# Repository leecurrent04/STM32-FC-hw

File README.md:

# NARAEON (나래온)

**NARAEON**은 인하대학교 모형항공기 동아리 '나래'(NARAE)에서 개발 중인 오픈소스 비행제어컴퓨터(FC) 프로젝트입니다. 이 프로젝트는 학술적 연구, 개발 그리고 취미 활동을 목적으로 하는 모든 분들을 위해 하드웨어, 펌웨어를 포함하고 있습니다.

## 🌟 프로젝트 소개
NARAEON은 무인항공기(UAV)의 핵심인 **비행제어컴퓨터**와 주요 센서들을 아우르는 통합 플랫폼입니다. 
저희는 항공전자 분야를 처음 배우는 학생들이 쉽게 학습하고 새로운 기능을 구현 및 창조할 수 있는 플랫폼을 제공하고자 이 프로젝트를 시작하게 되었습니다.

## ✨ 주요 특징
- 오픈소스: 하드웨어 회로도부터 펌웨어 소스 코드까지 모든 것이 공개되어 있어 누구나 자유롭게 사용하고, 수정하며, 기여할 수 있습니다.
- 통합 플랫폼: 비행 제어에 필요한 컴퓨터와 핵심 센서를 포함하여 안정적인 비행 제어 솔루션을 제공합니다.
- 확장성: 다양한 종류의 무인항공기에 적용할 수 있도록 설계되었으며, 사용자의 필요에 따라 기능을 쉽게 확장할 수 있습니다.
- 교육 및 연구: 학생, 연구자, 개발자들이 비행 제어 시스템의 원리를 깊이 있게 학습하고, 새로운 기술을 실험할 수 있는 훌륭한 교육 및 연구 도구입니다.

## 🚀 시작하기
프로젝트를 시작하는 데 필요한 정보는 각 저장소의 Wiki 페이지나 문서를 참고해 주세요. (링크 추가 예정)

하드웨어: [하드웨어 관련 저장소 링크]

- [STM32-FC](https://github.com/NARAE-INHA-UNIV/STM32-FC) : Firmware & Source code
- [NALDA](https://github.com/NARAE-INHA-UNIV/NALDA) : GCS

## 🔍 HW Spec.

> PCB 보드에 릴리즈 날짜와 버전이 기록되어 있지 않으면 v1.0.0 버전 입니다.
현재 최신 버전은 v1.1.0 입니다.

- ICM-45686 & ICM-42688-P dual IMU
- LIS2MDL eCompass
- ICP-20100 pressure sensor
- 내장 Flash memory & Micro SD card
- IBUS, SBUS, SRXL2, ELRS, PPM RC 프로토콜 지원

## 🤝 기여하기

NARAEON 프로젝트는 여러분의 참여를 언제나 환영합니다! 버그 리포트, 기능 제안, 코드 기여 등 어떤 형태의 기여도 프로젝트 발전에 큰 힘이 됩니다. 기여하고 싶으시다면 다음을 참고해 주세요.

1. 이 저장소를 Fork 하세요.
2. 새로운 기능이나 수정을 위한 Branch를 생성하세요 (git checkout -b feature/AmazingFeature).
3. 코드를 수정하고 Commit 하세요 (git commit -m 'Add some AmazingFeature').
4. Branch에 Push 하세요 (git push origin feature/AmazingFeature).
5. Pull Request를 열어주세요.

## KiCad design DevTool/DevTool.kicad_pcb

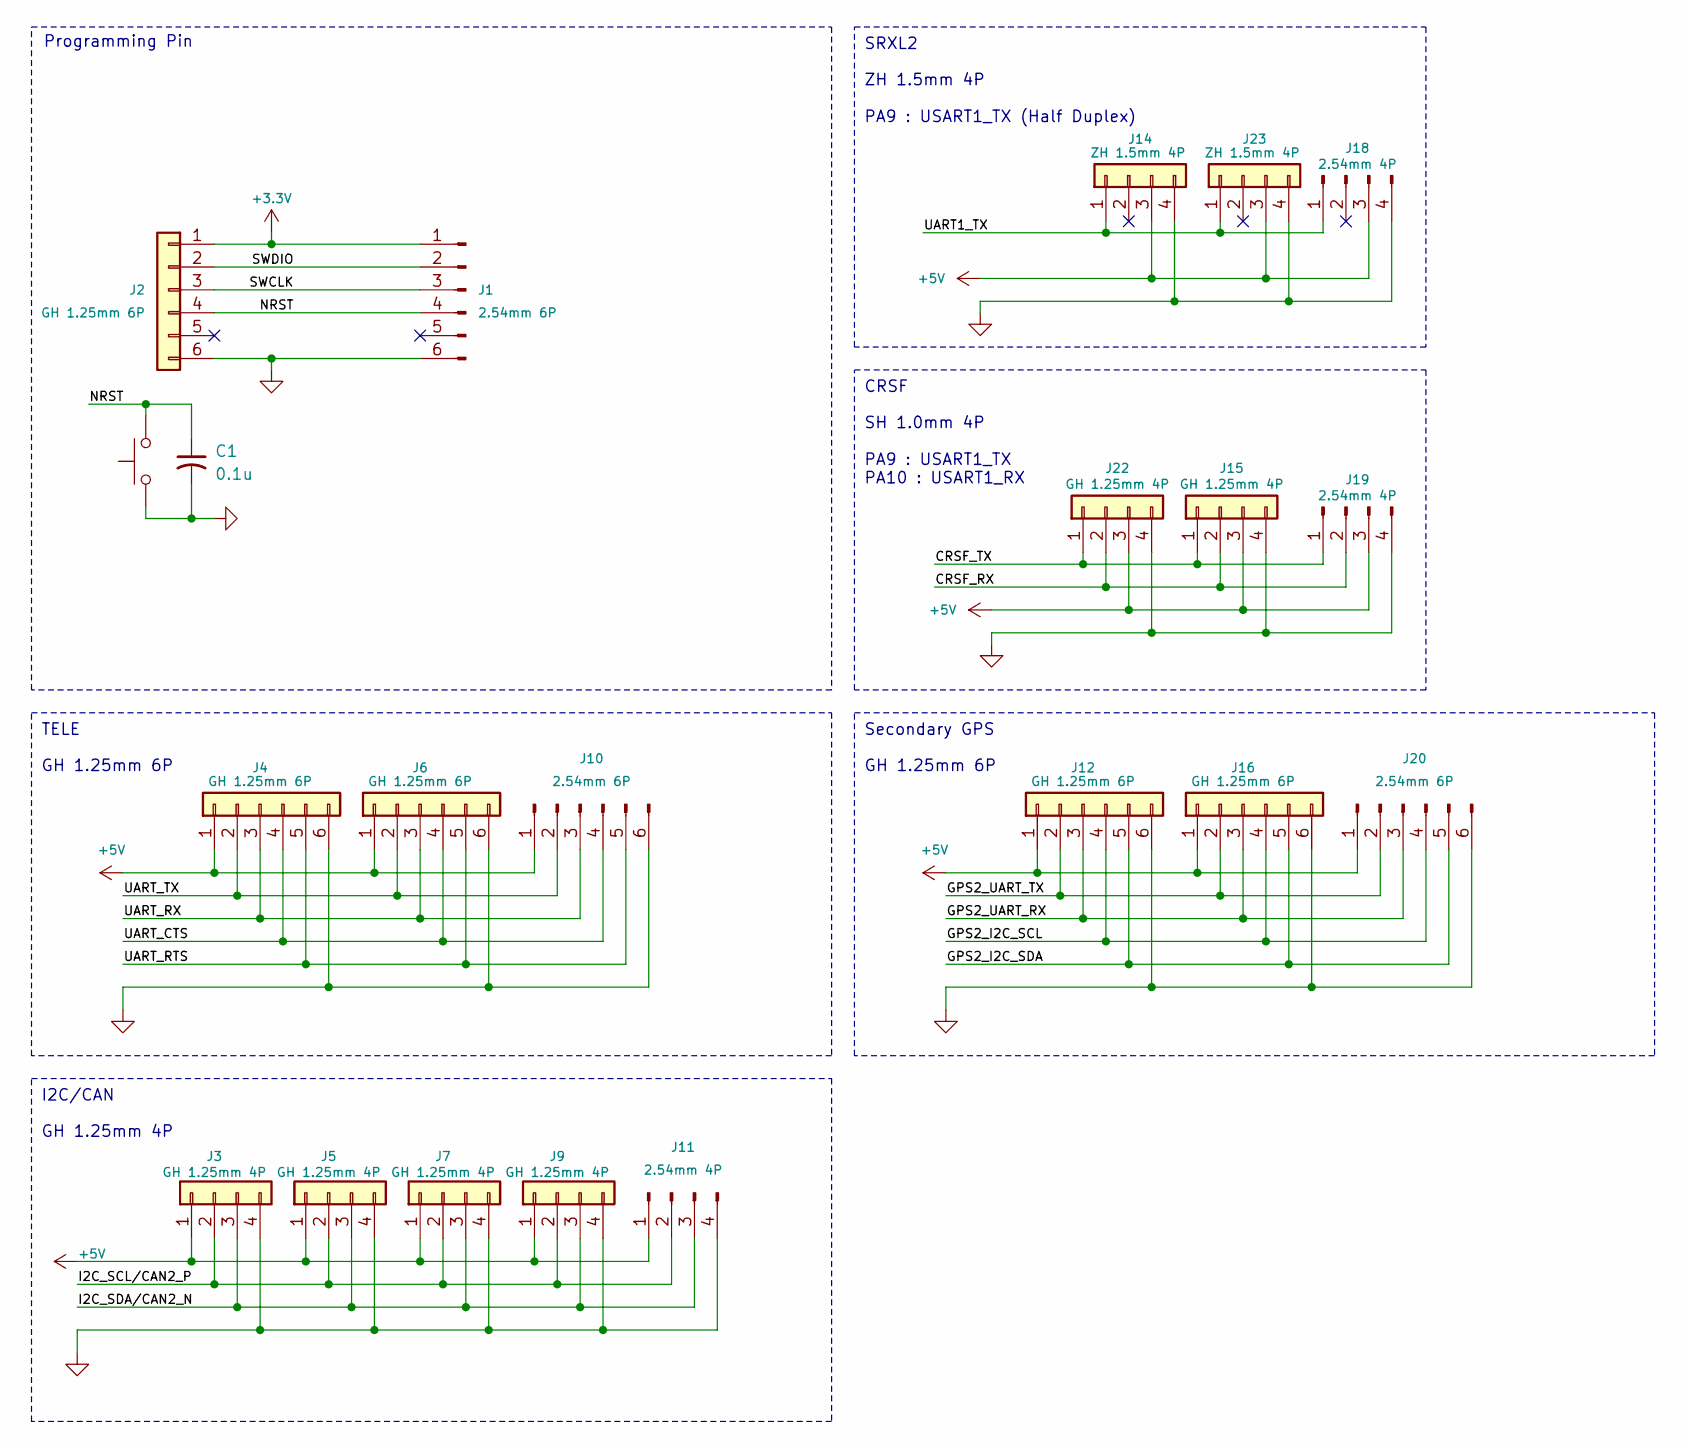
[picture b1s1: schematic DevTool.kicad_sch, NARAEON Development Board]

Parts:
C1: 0.1u; C_0603_1608Metric
J1, J10, J20: 2.54mm 6P; PinHeader_1x06_P2.54mm_Vertical
J2, J4, J6, J12, J16: GH 1.25mm 6P; JST_GH_BM06B-GHS-TBT_06; LCSC C133065
J3, J5, J7, J9, J15, J22: GH 1.25mm 4P; JST_GH_BM04B-GHS-TBT_04; LCSC C189895
J11, J18, J19: 2.54mm 4P; PinHeader_1x04_P2.54mm_Vertical
J14, J23: ZH 1.5mm 4P; JST_ZH_S4B-ZR-SM4A-TF_1x04-1MP_P1.50mm_Horizontal; LCSC C485354
SW1: SW_Push; SW_SPST_PTS645

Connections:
+3.3V: J1.1, J2.1
+5V: J3.1, J4.1, J5.1, J6.1, J7.1, J9.1, J10.1, J11.1, J12.1, J14.3, J15.3, J16.1, J18.3, J19.3, J20.1, J22.3, J23.3
/CRSF_RX: J15.2, J19.2, J22.2
/CRSF_TX: J15.1, J19.1, J22.1
/GPS2_I2C_SCL: J12.4, J16.4, J20.4
/GPS2_I2C_SDA: J12.5, J16.5, J20.5
/GPS2_UART_RX: J12.3, J16.3, J20.3
/GPS2_UART_TX: J12.2, J16.2, J20.2
/I2C_SCL/CAN2_P: J3.2, J5.2, J7.2, J9.2, J11.2
/I2C_SDA/CAN2_N: J3.3, J5.3, J7.3, J9.3, J11.3
/NRST: C1.1, J1.4, J2.4, SW1.2
/SWCLK: J1.3, J2.3
/SWDIO: J1.2, J2.2
/UART1_TX: J14.1, J18.1, J23.1
/UART_CTS: J4.4, J6.4, J10.4
/UART_RTS: J4.5, J6.5, J10.5
/UART_RX: J4.3, J6.3, J10.3
/UART_TX: J4.2, J6.2, J10.2
GND: C1.2, J1.6, J2.6, J3.4, J4.6, J5.4, J6.6, J7.4, J9.4, J10.6, J11.4, J12.6, J14.4, J15.4, J16.6, J18.4, J19.4, J20.6, J22.4, J23.4, SW1.1

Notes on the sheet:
SRXL2
CRSF
SH 1.0mm 4P PA9 : USART1_TX PA10 : USART1_RX
GH 1.25mm 6P
Programming Pin
TELE
GH 1.25mm 4P
I2C/CAN
Secondary GPS
ZH 1.5mm 4P PA9 : USART1_TX (Half Duplex)

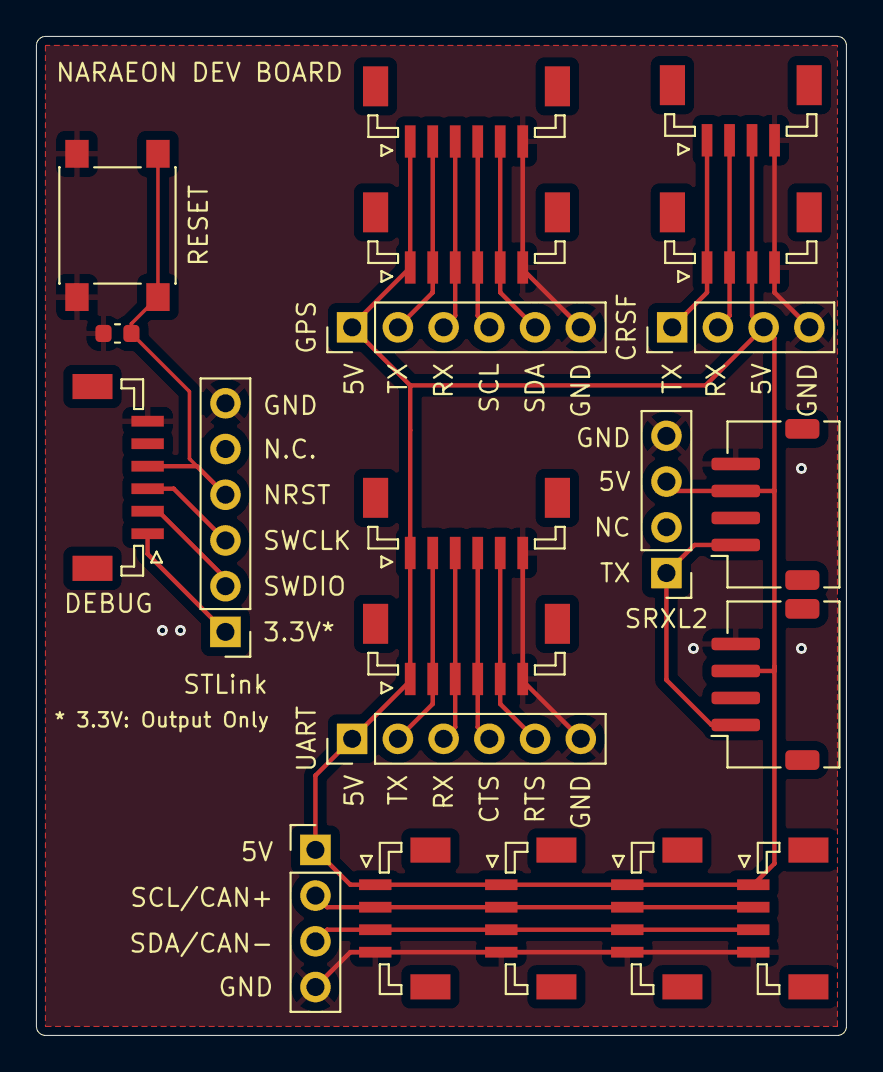
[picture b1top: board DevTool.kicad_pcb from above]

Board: 2 copper layers, 45.0 x 55.5 mm, 21 parts (0 on the bottom side), 19 nets.

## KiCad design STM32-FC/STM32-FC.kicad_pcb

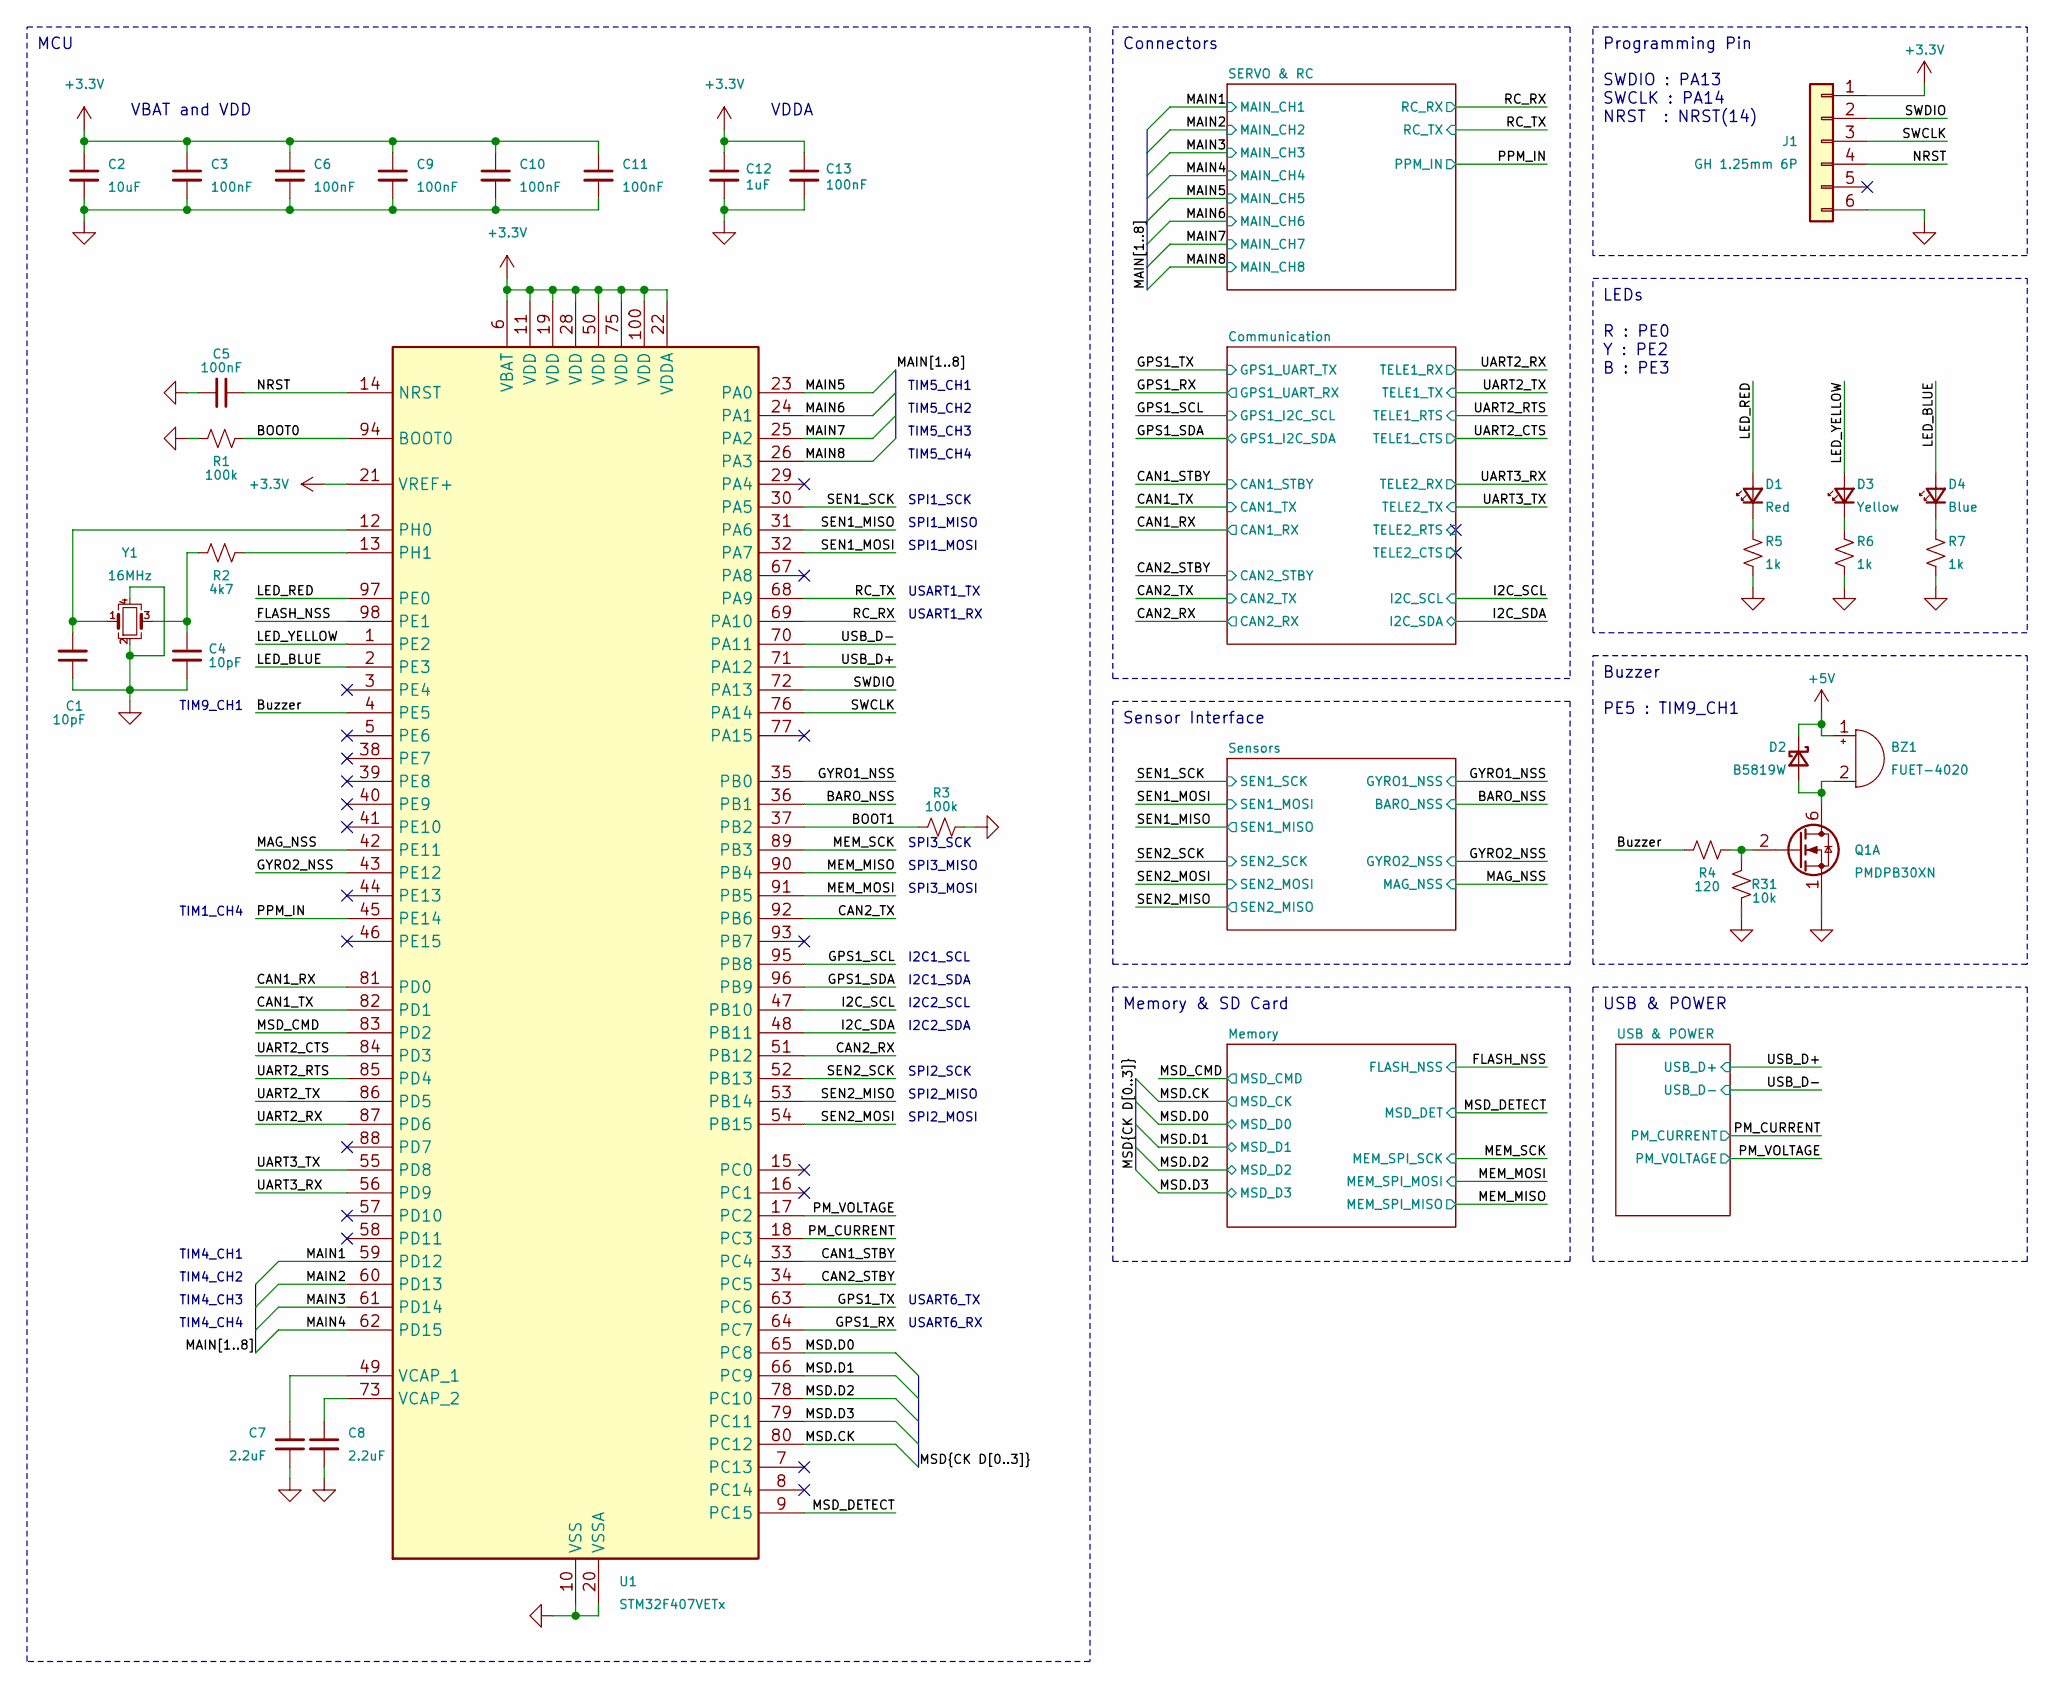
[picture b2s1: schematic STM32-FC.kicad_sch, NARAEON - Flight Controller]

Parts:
BZ1: FUET-4020; LCSC C391027
C1, C4: 10pF; C_0402_1005Metric; LCSC C1545
C2: 10uF; C_0402_1005Metric; LCSC C307415
C3, C5, C6, C9, C10, C11, C13: 100nF; C_0402_1005Metric; LCSC C1525
C7, C8: 2.2uF; C_0402_1005Metric; LCSC C170151
C12: 1uF; C_0402_1005Metric; LCSC C14445
D1: Red; LED_0402_1005Metric; LCSC C130719
D2: B5819W; D_SOD-323; LCSC C22624
D3: Yellow; LED_0402_1005Metric; LCSC C130721
D4: Blue; LED_0402_1005Metric; LCSC C130724
J1: GH 1.25mm 6P; JST_GH_BM06B-GHS-TBT_1x06-1MP_P1.25mm_Vertical; LCSC C189892
Q1: PMDPB30XN; Nexperia_SOT1118; LCSC C478009
R1, R3: 100k; R_0402_1005Metric; LCSC C25741
R2: 4k7; R_0402_1005Metric; LCSC C25900
R4: 120; R_0402_1005Metric; LCSC C25079
R5, R6, R7: 1k; R_0402_1005Metric; LCSC C11702
R31: 10k; R_0402_1005Metric; LCSC C25531
U1: STM32F407VETx; LQFP-100_14x14mm_P0.5mm; LCSC C28730
Y1: 16MHz; Crystal_SMD_Abracon_ABM8G-4Pin_3.2x2.5mm; LCSC C1985423

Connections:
+3.3V: C2.1, C3.1, C6.1, C9.1, C10.1, C11.1, C12.1, C13.1, J1.1, U1.6 (VBAT), U1.11 (VDD), U1.19 (VDD), U1.21 (VREF+), U1.22 (VDDA), U1.28 (VDD), U1.50 (VDD), U1.75 (VDD), U1.100 (VDD); also elsewhere on the board
+5V: BZ1.1 (-), D2.1 (K); also elsewhere on the board
/BARO_NSS: U1.36 (PB1); also elsewhere on the board
/BOOT0: R1.2, U1.94 (BOOT0)
/BOOT1: R3.2, U1.37 (PB2)
/Buzzer: R4.1, U1.4 (PE5)
/CAN1_RX: U1.81 (PD0); also elsewhere on the board
/CAN1_STBY: U1.33 (PC4); also elsewhere on the board
/CAN1_TX: U1.82 (PD1); also elsewhere on the board
/CAN2_RX: U1.51 (PB12); also elsewhere on the board
/CAN2_STBY: U1.34 (PC5); also elsewhere on the board
/CAN2_TX: U1.92 (PB6); also elsewhere on the board
/FLASH_NSS: U1.98 (PE1); also elsewhere on the board
/GPS1_RX: U1.64 (PC7); also elsewhere on the board
/GPS1_SCL: U1.95 (PB8); also elsewhere on the board
/GPS1_SDA: U1.96 (PB9); also elsewhere on the board
/GPS1_TX: U1.63 (PC6); also elsewhere on the board
/GYRO1_NSS: U1.35 (PB0); also elsewhere on the board
/GYRO2_NSS: U1.43 (PE12); also elsewhere on the board
/I2C1_SCL: U1.47 (PB10); also elsewhere on the board
/I2C1_SDA: U1.48 (PB11); also elsewhere on the board
/LED_BLUE: D4.2 (A), U1.2 (PE3)
/LED_RED: D1.2 (A), U1.97 (PE0)
/LED_YELLOW: D3.2 (A), U1.1 (PE2)
/MAG_NSS: U1.42 (PE11); also elsewhere on the board
/MAIN1: U1.59 (PD12); also elsewhere on the board
/MAIN2: U1.60 (PD13); also elsewhere on the board
/MAIN3: U1.61 (PD14); also elsewhere on the board
/MAIN4: U1.62 (PD15); also elsewhere on the board
/MAIN5: U1.23 (PA0); also elsewhere on the board
/MAIN6: U1.24 (PA1); also elsewhere on the board
/MAIN7: U1.25 (PA2); also elsewhere on the board
/MAIN8: U1.26 (PA3); also elsewhere on the board
/MEM_MISO: U1.90 (PB4); also elsewhere on the board
/MEM_MOSI: U1.91 (PB5); also elsewhere on the board
/MEM_SCK: U1.89 (PB3); also elsewhere on the board
/MSD.CK: U1.80 (PC12); also elsewhere on the board
/MSD.D0: U1.65 (PC8); also elsewhere on the board
/MSD.D1: U1.66 (PC9); also elsewhere on the board
/MSD.D2: U1.78 (PC10); also elsewhere on the board
/MSD.D3: U1.79 (PC11); also elsewhere on the board
/MSD_CMD: U1.83 (PD2); also elsewhere on the board
/MSD_DETECT: U1.9 (PC15); also elsewhere on the board
/NRST: C5.1, J1.4, U1.14 (NRST)
/PM_CURRENT: U1.18 (PC3); also elsewhere on the board
/PM_VOLTAGE: U1.17 (PC2); also elsewhere on the board
/PPM_IN: U1.45 (PE14); also elsewhere on the board
/RC_RX: U1.69 (PA10); also elsewhere on the board
/RC_TX: U1.68 (PA9); also elsewhere on the board
/SEN1_MISO: U1.31 (PA6); also elsewhere on the board
/SEN1_MOSI: U1.32 (PA7); also elsewhere on the board
/SEN1_SCK: U1.30 (PA5); also elsewhere on the board
/SEN2_MISO: U1.53 (PB14); also elsewhere on the board
/SEN2_MOSI: U1.54 (PB15); also elsewhere on the board
/SEN2_SCK: U1.52 (PB13); also elsewhere on the board
/SWCLK: J1.3, U1.76 (PA14)
/SWDIO: J1.2, U1.72 (PA13)
/UART2_CTS: U1.84 (PD3); also elsewhere on the board
/UART2_RTS: U1.85 (PD4); also elsewhere on the board
/UART2_RX: U1.87 (PD6); also elsewhere on the board
/UART2_TX: U1.86 (PD5); also elsewhere on the board
/UART3_RX: U1.56 (PD9); also elsewhere on the board
/UART3_TX: U1.55 (PD8); also elsewhere on the board
/USB_D+: U1.71 (PA12); also elsewhere on the board
/USB_D-: U1.70 (PA11); also elsewhere on the board
GND: C1.1, C2.2, C3.2, C4.2, C5.2, C6.2, C7.1, C8.2, C9.2, C10.2, C11.2, C12.2, C13.2, J1.6, Q1.1 (S), R1.1, R3.1, R5.2, R6.2, R7.2, R31.2, U1.10 (VSS), U1.20 (VSSA), U1.27 (VSS), U1.74 (VSS), U1.99 (VSS), Y1.2, Y1.4; also elsewhere on the board
unnamed: BZ1.2 (+), D2.2 (A), Q1.6 (D), Q1.7 (D)
unnamed: C4.1, R2.1, Y1.3
unnamed: D1.1 (K), R5.1
unnamed: D3.1 (K), R6.1
unnamed: D4.1 (K), R7.1
unnamed: Q1.2 (G), R4.2, R31.1
unnamed: C1.2, U1.12 (PH0), Y1.1
unnamed: R2.2, U1.13 (PH1)
unnamed: C7.2, U1.49 (VCAP_1)
unnamed: C8.1, U1.73 (VCAP_2)

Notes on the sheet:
Connectors
PE5 : TIM9_CH1
TIM9_CH1
TIM5_CH1
TIM4_CH3
SPI3_SCK
SPI3_MISO
TIM4_CH1
I2C2_SCL
USART6_RX
TIM4_CH2
MCU
VDDA
USART1_TX
SPI2_MOSI
SPI3_MOSI
Buzzer
TIM1_CH4
I2C1_SCL
USART1_RX
TIM5_CH3
Sensor Interface
LEDs
Programming Pin
TIM5_CH4
Memory & SD Card
USB & POWER
SPI1_MOSI
I2C1_SDA
USART6_TX
R : PE0 Y : PE2 B : PE3
TIM4_CH4
TIM5_CH2
SPI2_SCK
SWDIO : PA13 SWCLK : PA14 NRST : NRST(14)
SPI1_MISO
I2C2_SDA
VBAT and VDD
SPI2_MISO
SPI1_SCK

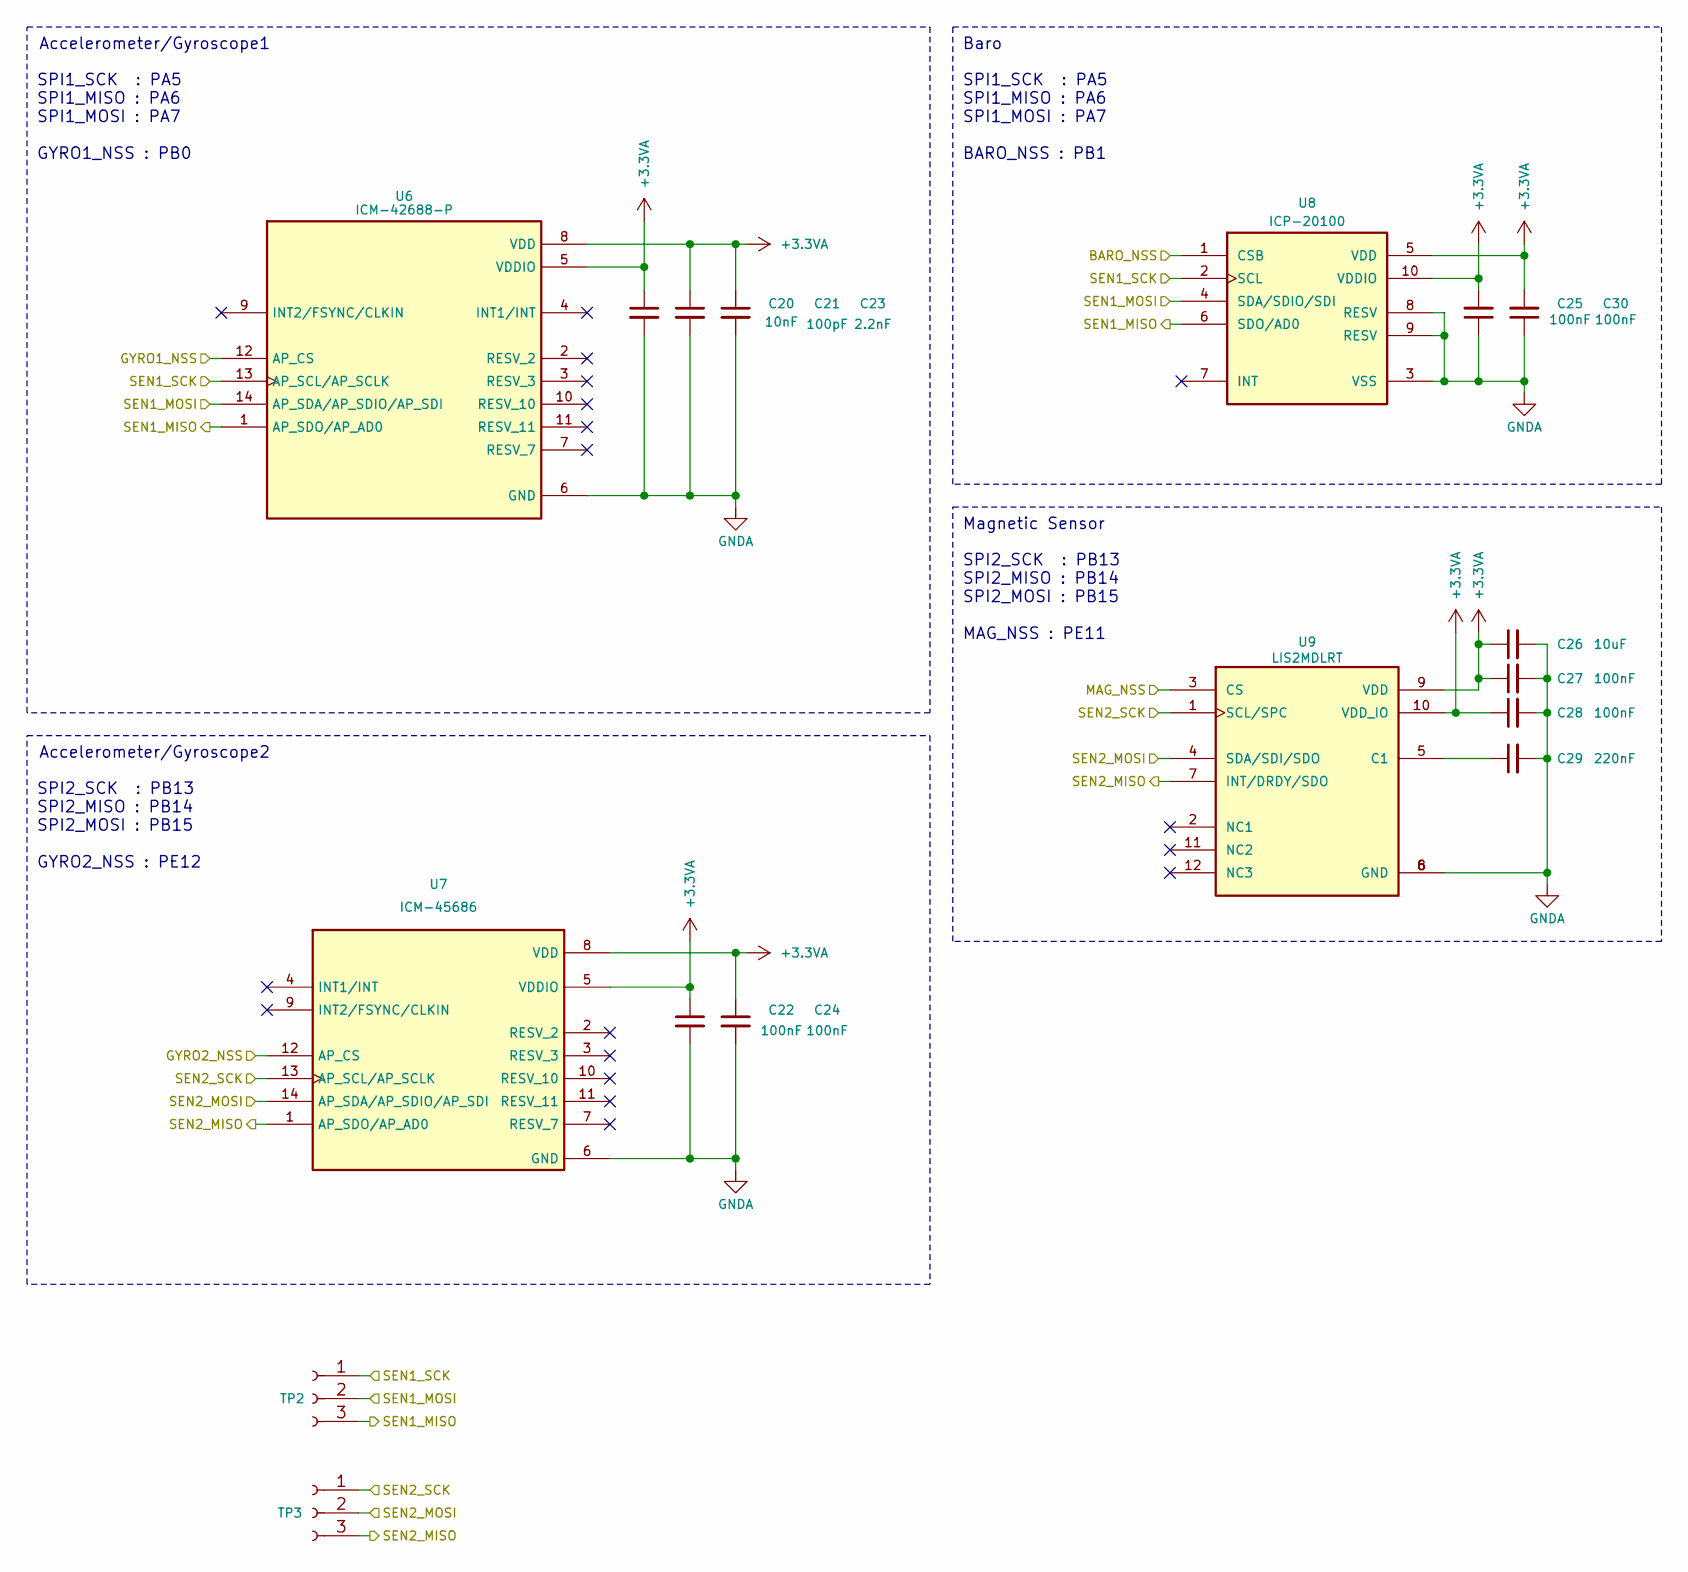
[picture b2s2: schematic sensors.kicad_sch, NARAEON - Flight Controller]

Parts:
C20: 10nF; C_0402_1005Metric; LCSC C15195
C21: 100pF; C_0402_1005Metric; LCSC C152819
C22, C24, C25, C27, C28, C30: 100nF; C_0402_1005Metric; LCSC C1525
C23: 2.2nF; C_0402_1005Metric; LCSC C84703
C26: 10uF; C_0402_1005Metric; LCSC C307415
C29: 220nF; C_0402_1005Metric; LCSC C16651
TP2, TP3: Test Pin; PinHeader_1x03_P1.27mm_Vertical; LCSC C24980
U6: ICM-42688-P; IIM42352_L; LCSC C1850418
U7: ICM-45686; LCSC C22459454
U8: ICP-20100; LCSC C5343527
U9: LIS2MDLRT; LIS2MDLTR; PARTREV Rev 5; LCSC C919695

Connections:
+3.3VA: C20.1, C21.1, C22.1, C23.1, C24.1, C25.2, C26.1, C27.1, C28.1, C30.2, U6.5 (VDDIO), U6.8 (VDD), U7.5 (VDDIO), U7.8 (VDD), U8.5 (VDD), U8.10 (VDDIO), U9.9 (VDD), U9.10 (VDD_IO); also elsewhere on the board
/BARO_NSS: U8.1 (CSB); also elsewhere on the board
/GYRO1_NSS: U6.12 (AP_CS); also elsewhere on the board
/GYRO2_NSS: U7.12 (AP_CS); also elsewhere on the board
/MAG_NSS: U9.3 (CS); also elsewhere on the board
/SEN1_MISO: TP2.3, U6.1 (AP_SDO/AP_AD0), U8.6 (SDO/AD0); also elsewhere on the board
/SEN1_MOSI: TP2.2, U6.14 (AP_SDA/AP_SDIO/AP_SDI), U8.4 (SDA/SDIO/SDI); also elsewhere on the board
/SEN1_SCK: TP2.1, U6.13 (AP_SCL/AP_SCLK), U8.2 (SCL); also elsewhere on the board
/SEN2_MISO: TP3.3, U7.1 (AP_SDO/AP_AD0), U9.7 (INT/DRDY/SDO); also elsewhere on the board
/SEN2_MOSI: TP3.2, U7.14 (AP_SDA/AP_SDIO/AP_SDI), U9.4 (SDA/SDI/SDO); also elsewhere on the board
/SEN2_SCK: TP3.1, U7.13 (AP_SCL/AP_SCLK), U9.1 (SCL/SPC); also elsewhere on the board
GNDA: C20.2, C21.2, C22.2, C23.2, C24.2, C25.1, C26.2, C27.2, C28.2, C29.2, C30.1, U6.6 (GND), U7.6 (GND), U8.3 (VSS), U8.8 (RESV), U8.9 (RESV), U9.6 (GND), U9.8 (GND); also elsewhere on the board
unnamed: C29.1, U9.5 (C1)

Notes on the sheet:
Magnetic Sensor
Accelerometer/Gyroscope1
SPI2_SCK : PB13 SPI2_MISO : PB14 SPI2_MOSI : PB15 GYRO2_NSS : PE12
SPI1_SCK : PA5 SPI1_MISO : PA6 SPI1_MOSI : PA7 GYRO1_NSS : PB0
SPI1_SCK : PA5 SPI1_MISO : PA6 SPI1_MOSI : PA7 BARO_NSS : PB1
Accelerometer/Gyroscope2
SPI2_SCK : PB13 SPI2_MISO : PB14 SPI2_MOSI : PB15 MAG_NSS : PE11
Baro

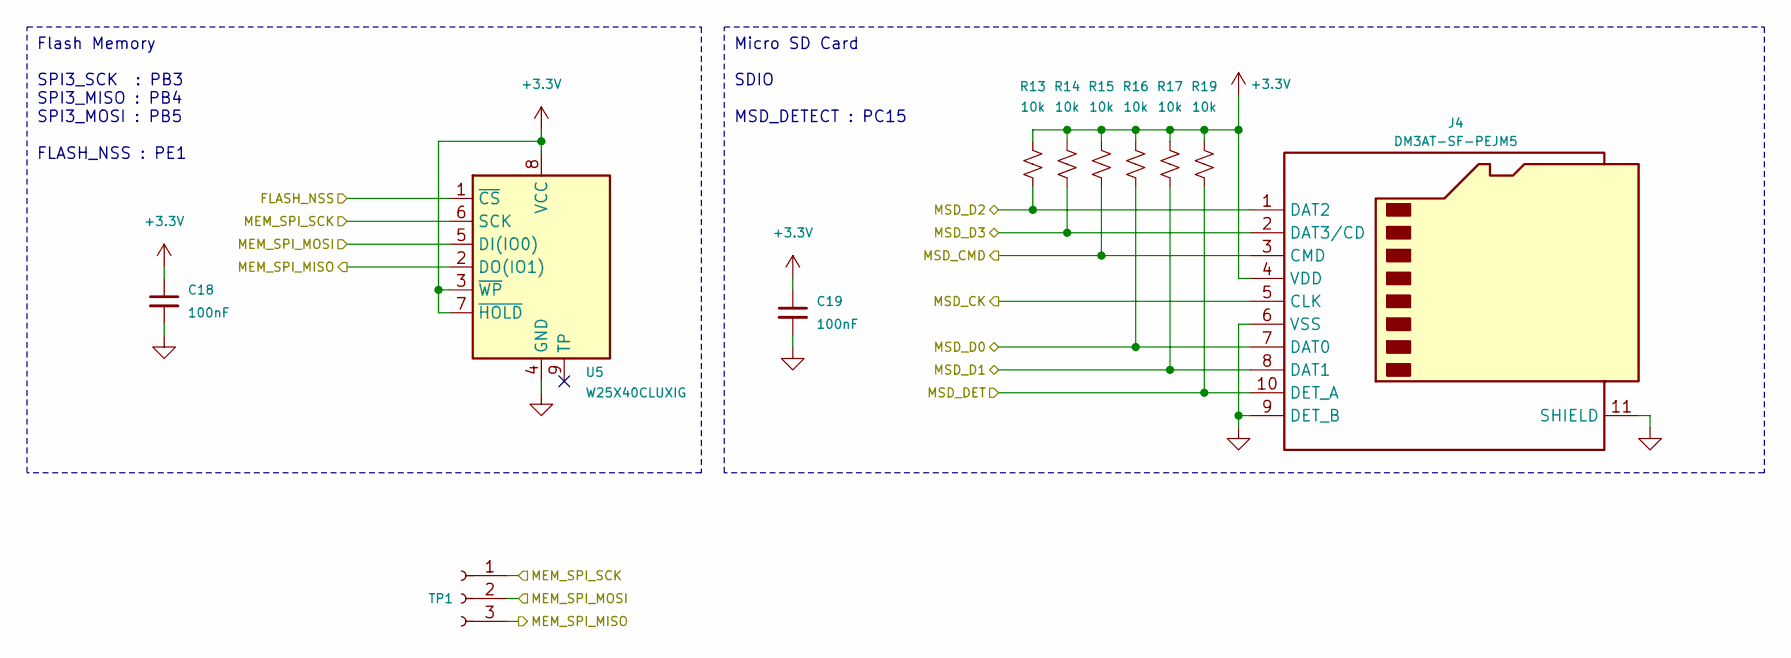
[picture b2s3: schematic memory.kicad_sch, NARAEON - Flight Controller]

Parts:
C18, C19: 100nF; C_0402_1005Metric; LCSC C1525
J4: DM3AT-SF-PEJM5; microSD_HC_Hirose_DM3AT-SF-PEJM5; LCSC C114218
R13, R14, R15, R16, R17, R19: 10k; R_0402_1005Metric; LCSC C25531
TP1: Test Pin; PinHeader_1x03_P1.27mm_Vertical; LCSC C24980
U5: W25X40CLUXIG; USON_LUXIG TR_WIN; LCSC C401661

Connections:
+3.3V: C18.1, C19.1, J4.4 (VDD), R13.1, R14.1, R15.1, R16.1, R17.1, R19.1, U5.3 (~WP), U5.7 (~HOLD), U5.8 (VCC); also elsewhere on the board
/FLASH_NSS: U5.1 (~CS); also elsewhere on the board
/MEM_MISO: TP1.3, U5.2 (DO(IO1)); also elsewhere on the board
/MEM_MOSI: TP1.2, U5.5 (DI(IO0)); also elsewhere on the board
/MEM_SCK: TP1.1, U5.6 (SCK); also elsewhere on the board
/MSD.CK: J4.5 (CLK); also elsewhere on the board
/MSD.D0: J4.7 (DAT0), R16.2; also elsewhere on the board
/MSD.D1: J4.8 (DAT1), R17.2; also elsewhere on the board
/MSD.D2: J4.1 (DAT2), R13.2; also elsewhere on the board
/MSD.D3: J4.2 (DAT3/CD), R14.2; also elsewhere on the board
/MSD_CMD: J4.3 (CMD), R15.2; also elsewhere on the board
/MSD_DETECT: J4.10 (DET_A), R19.2; also elsewhere on the board
GND: C18.2, C19.2, J4.6 (VSS), J4.9 (DET_B), J4.11 (SHIELD), U5.4 (GND); also elsewhere on the board

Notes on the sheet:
SDIO MSD_DETECT : PC15
SPI3_SCK : PB3 SPI3_MISO : PB4 SPI3_MOSI : PB5 FLASH_NSS : PE1
Flash Memory
Micro SD Card

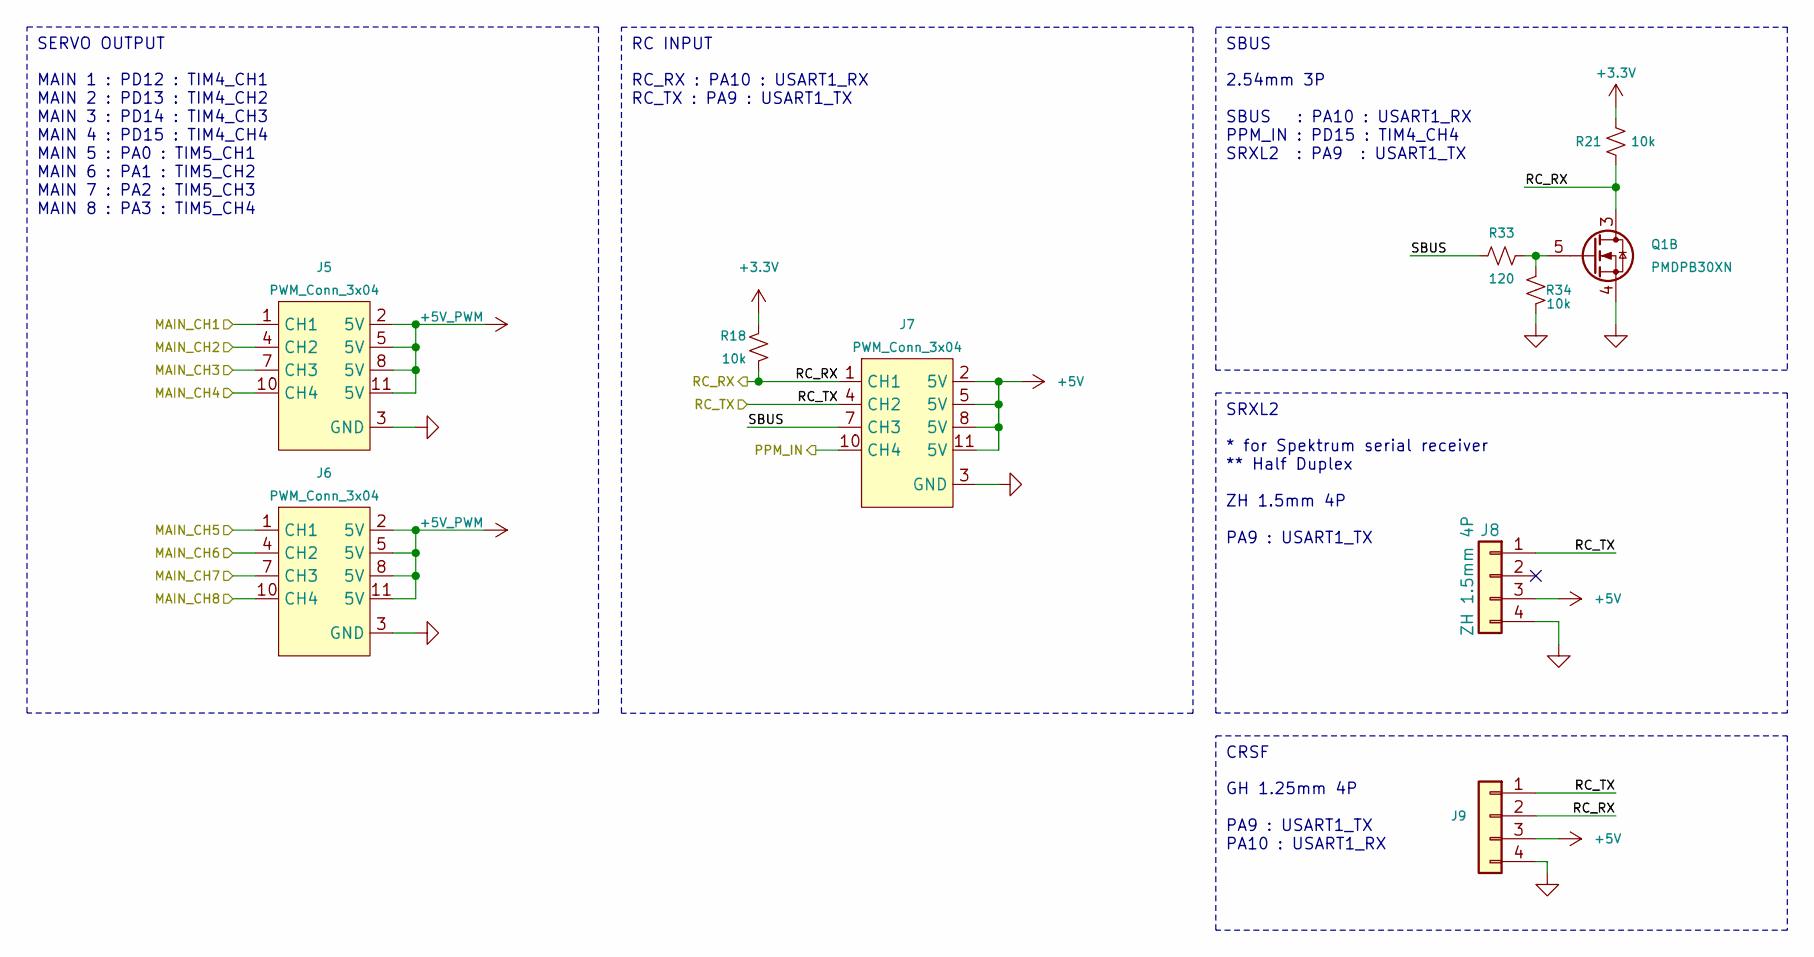
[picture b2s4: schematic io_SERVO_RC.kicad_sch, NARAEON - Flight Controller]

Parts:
J5, J6, J7: PWM_Conn_3x04; PWM_Conn_3x04_JLC; LCSC C3325573
J8: ZH 1.5mm 4P; JST_ZH_B4B-ZR-SM4-TF_1x04-1MP_P1.50mm_Vertical; LCSC C485354
J9: GH 1.25mm 4P; JST_GH_BM04B-GHS-TBT_1x04-1MP_P1.25mm_Vertical; LCSC C161692
Q1: PMDPB30XN; Nexperia_SOT1118; LCSC C478009
R18, R21, R34: 10k; R_0402_1005Metric; LCSC C25531
R33: 120; R_0402_1005Metric; LCSC C25079

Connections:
+3.3V: R18.1, R21.1; also elsewhere on the board
+5V: J7.2 (5V), J7.5 (5V), J7.8 (5V), J7.11 (5V), J8.3, J9.3; also elsewhere on the board
+5V_PWM: J5.2 (5V), J5.5 (5V), J5.8 (5V), J5.11 (5V), J6.2 (5V), J6.5 (5V), J6.8 (5V), J6.11 (5V); also elsewhere on the board
/MAIN1: J5.1 (CH1); also elsewhere on the board
/MAIN2: J5.4 (CH2); also elsewhere on the board
/MAIN3: J5.7 (CH3); also elsewhere on the board
/MAIN4: J5.10 (CH4); also elsewhere on the board
/MAIN5: J6.1 (CH1); also elsewhere on the board
/MAIN6: J6.4 (CH2); also elsewhere on the board
/MAIN7: J6.7 (CH3); also elsewhere on the board
/MAIN8: J6.10 (CH4); also elsewhere on the board
/PPM_IN: J7.10 (CH4); also elsewhere on the board
/RC_RX: J7.1 (CH1), J9.2, Q1.3 (D), Q1.8 (D), R18.2, R21.2; also elsewhere on the board
/RC_TX: J7.4 (CH2), J8.1, J9.1; also elsewhere on the board
/SERVO & RC/SBUS: J7.7 (CH3), R33.1
GND: J5.3 (GND), J5.6 (GND), J5.9 (GND), J5.12 (GND), J6.3 (GND), J6.6 (GND), J6.9 (GND), J6.12 (GND), J7.3 (GND), J7.6 (GND), J7.9 (GND), J7.12 (GND), J8.4, J9.4, Q1.4 (S), R34.2; also elsewhere on the board
unnamed: Q1.5 (G), R33.2, R34.1

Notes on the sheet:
SBUS
SRXL2
2.54mm 3P SBUS : PA10 : USART1_RX PPM_IN : PD15 : TIM4_CH4 SRXL2 : PA9 : USART1_TX
RC INPUT
RC_RX : PA10 : USART1_RX RC_TX : PA9 : USART1_TX
MAIN 1 : PD12 : TIM4_CH1 MAIN 2 : PD13 : TIM4_CH2 MAIN 3 : PD14 : TIM4_CH3 MAIN 4 : PD15 : TIM4_CH4 MAIN 5 : PA0 : TIM5_CH1 MAIN 6 : PA1 : TIM5_CH2 MAIN 7 : PA2 : TIM5_CH3 MAIN 8 : PA3 : TIM5_CH4
SERVO OUTPUT
CRSF
* for Spektrum serial receiver ** Half Duplex ZH 1.5mm 4P PA9 : USART1_TX
GH 1.25mm 4P PA9 : USART1_TX PA10 : USART1_RX
